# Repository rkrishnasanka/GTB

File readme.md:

First KiCAD project following the tutorial from Contextual Electronics[http://www.contextualelectronics.com]

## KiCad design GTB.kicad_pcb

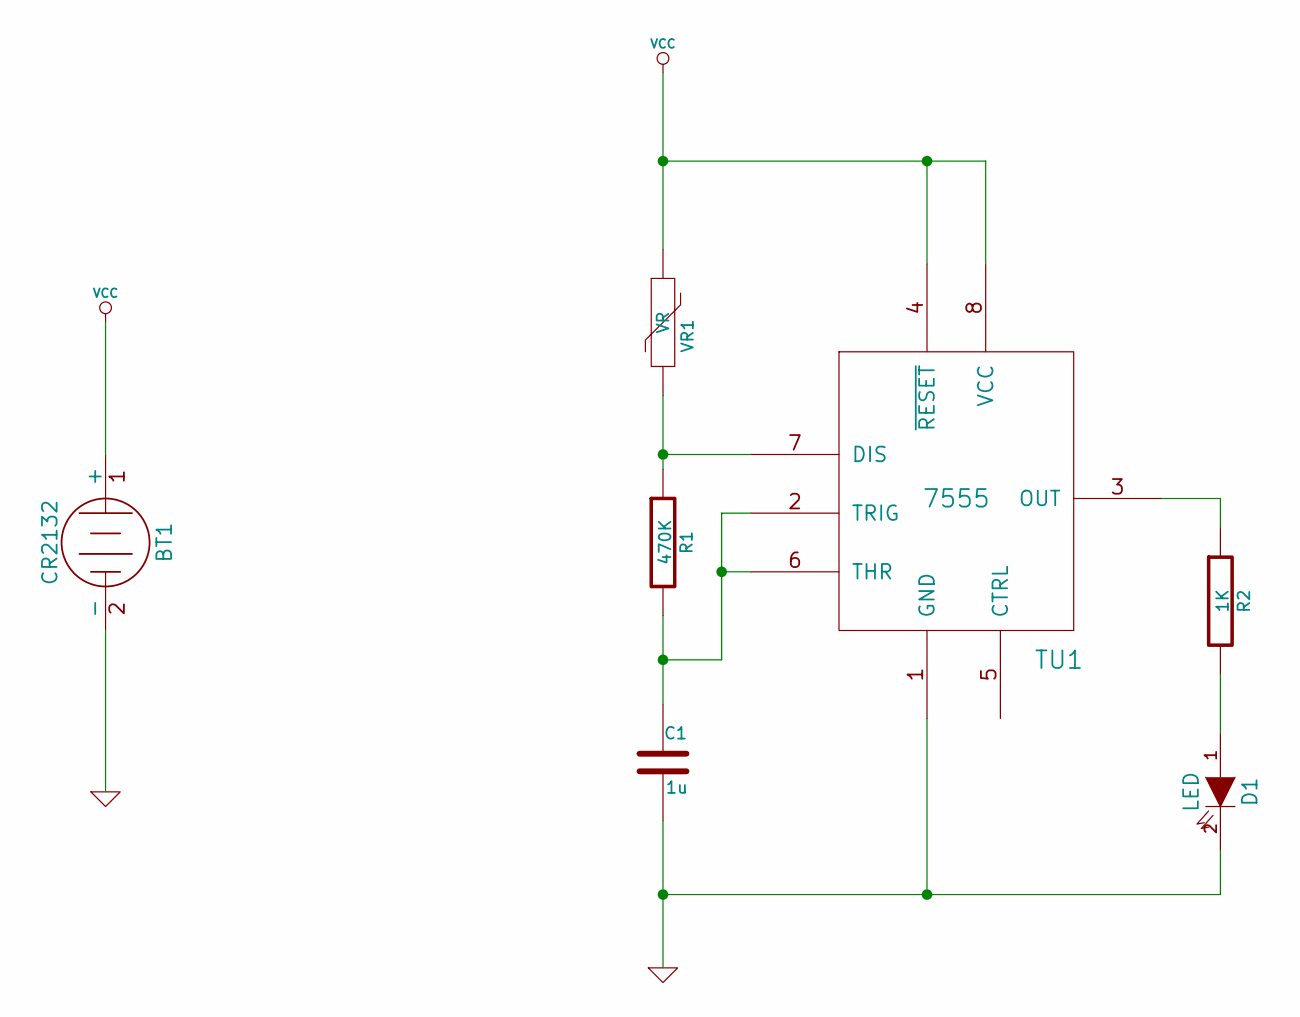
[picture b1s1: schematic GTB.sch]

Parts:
BT1: CR2132
C1: 1u
D1: LED
R1: 470K
R2: 1K
TU1: 7555
VR1: VR

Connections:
GND: BT1.2 (-), C1.2, D1.2 (K), TU1.1 (GND)
unnamed: C1.1, R1.2, TU1.2 (TRIG), TU1.6 (THR)
unnamed: R2.1, TU1.3 (OUT)
unnamed: D1.1 (A), R2.2
unnamed: R1.1, TU1.7 (DIS), VR1.2
VCC: BT1.1 (+), TU1.4 (~RESET), TU1.8 (VCC), VR1.1

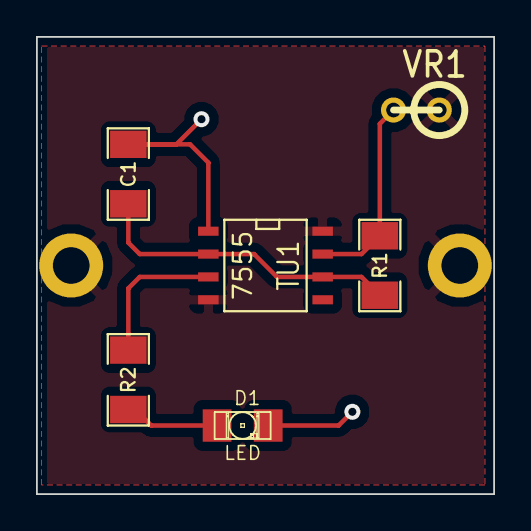
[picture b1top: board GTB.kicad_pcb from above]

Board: 2 copper layers, 25.4 x 25.4 mm, 7 parts (1 on the bottom side), 6 nets.

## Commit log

2014-01-21 Completed Tutorial
2014-01-21 Added .gitattributes and readme.md
